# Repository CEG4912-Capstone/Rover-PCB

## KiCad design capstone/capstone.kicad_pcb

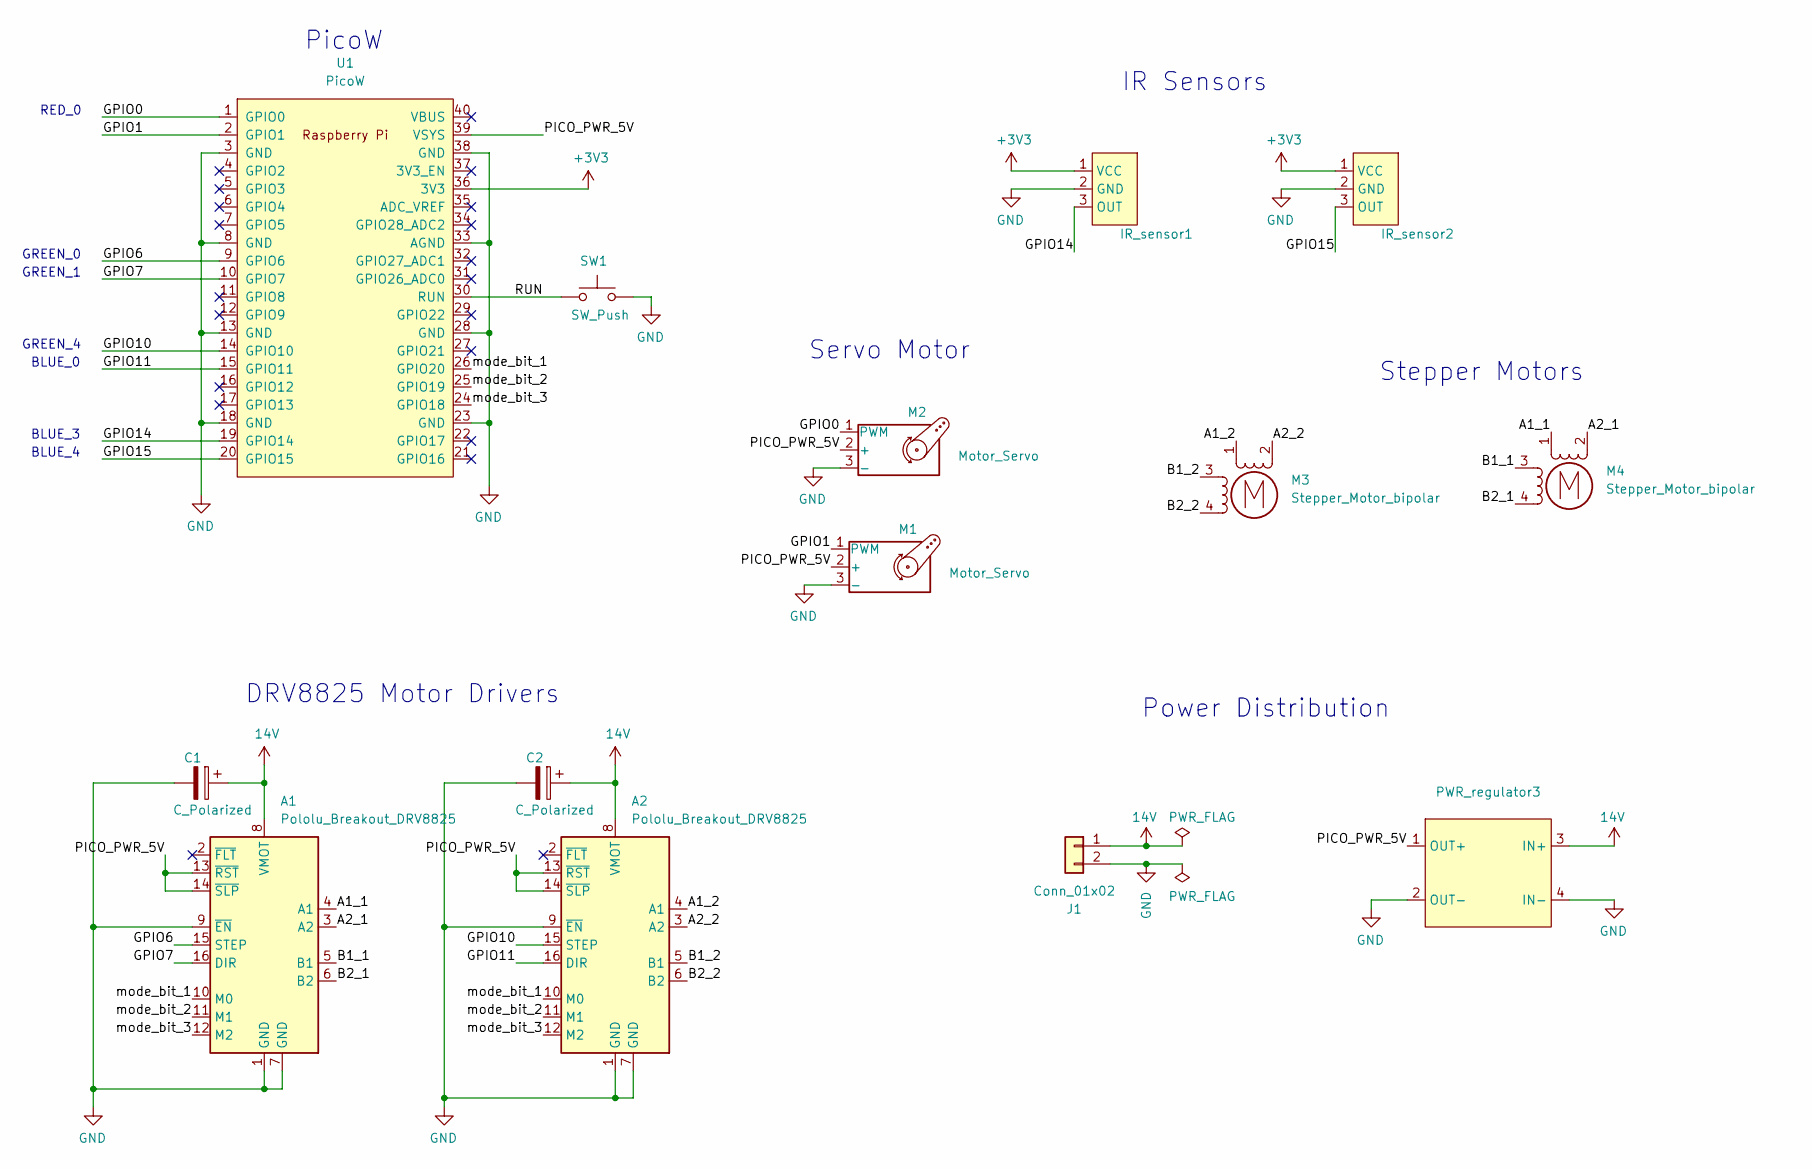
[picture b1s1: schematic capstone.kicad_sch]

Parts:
A1, A2: Pololu_Breakout_DRV8825; Pololu_Breakout-16_15.2x20.3mm
C1, C2: C_Polarized; CP_Radial_D6.3mm_P2.50mm
IR_sensor1, IR_sensor2: PinHeader_1x03_P2.54mm_Vertical
J1: Conn_01x02; AMASS_XT60PW-M_1x02_P7.20mm_Horizontal
M1, M2: Motor_Servo; PinHeader_1x03_P2.54mm_Horizontal
M3, M4: Stepper_Motor_bipolar; PinHeader_1x04_P2.54mm_Horizontal
PWR_regulator3: YAAJ_DCDC_StepDown_LM2596
SW1: SW_Push; SW_Push_1P1T_NO_Vertical_Wuerth_434133025816
U1: PicoW; RPi_PicoW_SMD_TH

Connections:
14V: A1.8 (VMOT), A2.8 (VMOT), C1.1, C2.1, J1.1, PWR_regulator3.3 (IN+)
+3V3: IR_sensor1.1 (VCC), IR_sensor2.1 (VCC), U1.36 (3V3)
/A1_1: A1.4 (A1), M4.1
/A1_2: A2.4 (A1), M3.1
/A2_1: A1.3 (A2), M4.2 (-)
/A2_2: A2.3 (A2), M3.2 (-)
/B1_1: A1.5 (B1), M4.3
/B1_2: A2.5 (B1), M3.3
/B2_1: A1.6 (B2), M4.4
/B2_2: A2.6 (B2), M3.4
/GPIO0: M2.1 (PWM), U1.1 (GPIO0)
/GPIO1: M1.1 (PWM), U1.2 (GPIO1)
/GPIO6: A1.15 (STEP), U1.9 (GPIO6)
/GPIO7: A1.16 (DIR), U1.10 (GPIO7)
/GPIO10: A2.15 (STEP), U1.14 (GPIO10)
/GPIO11: A2.16 (DIR), U1.15 (GPIO11)
/GPIO14: IR_sensor1.3 (OUT), U1.19 (GPIO14)
/GPIO15: IR_sensor2.3 (OUT), U1.20 (GPIO15)
/PICO_PWR_5V: A1.13 (~RST), A1.14 (~SLP), A2.13 (~RST), A2.14 (~SLP), M1.2 (+), M2.2 (+), PWR_regulator3.1 (OUT+), U1.39 (VSYS)
/RUN: SW1.1, U1.30 (RUN)
/mode_bit_1: A1.10 (M0), A2.10 (M0), U1.26 (GPIO20)
/mode_bit_2: A1.11 (M1), A2.11 (M1), U1.25 (GPIO19)
/mode_bit_3: A1.12 (M2), A2.12 (M2), U1.24 (GPIO18)
GND: A1.1 (GND), A1.7 (GND), A1.9 (~EN), A2.1 (GND), A2.7 (GND), A2.9 (~EN), C1.2, C2.2, IR_sensor1.2 (GND), IR_sensor2.2 (GND), J1.2, M1.3 (-), M2.3 (-), PWR_regulator3.2 (OUT-), PWR_regulator3.4 (IN-), SW1.2, U1.3 (GND), U1.8 (GND), U1.13 (GND), U1.18 (GND), U1.23 (GND), U1.28 (GND), U1.33 (AGND), U1.38 (GND)

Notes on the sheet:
BLUE_0
IR Sensors
DRV8825 Motor Drivers
Power Distribution
Servo Motor
GREEN_0
GREEN_4
PicoW
BLUE_4
GREEN_1
Stepper Motors
BLUE_3
RED_0

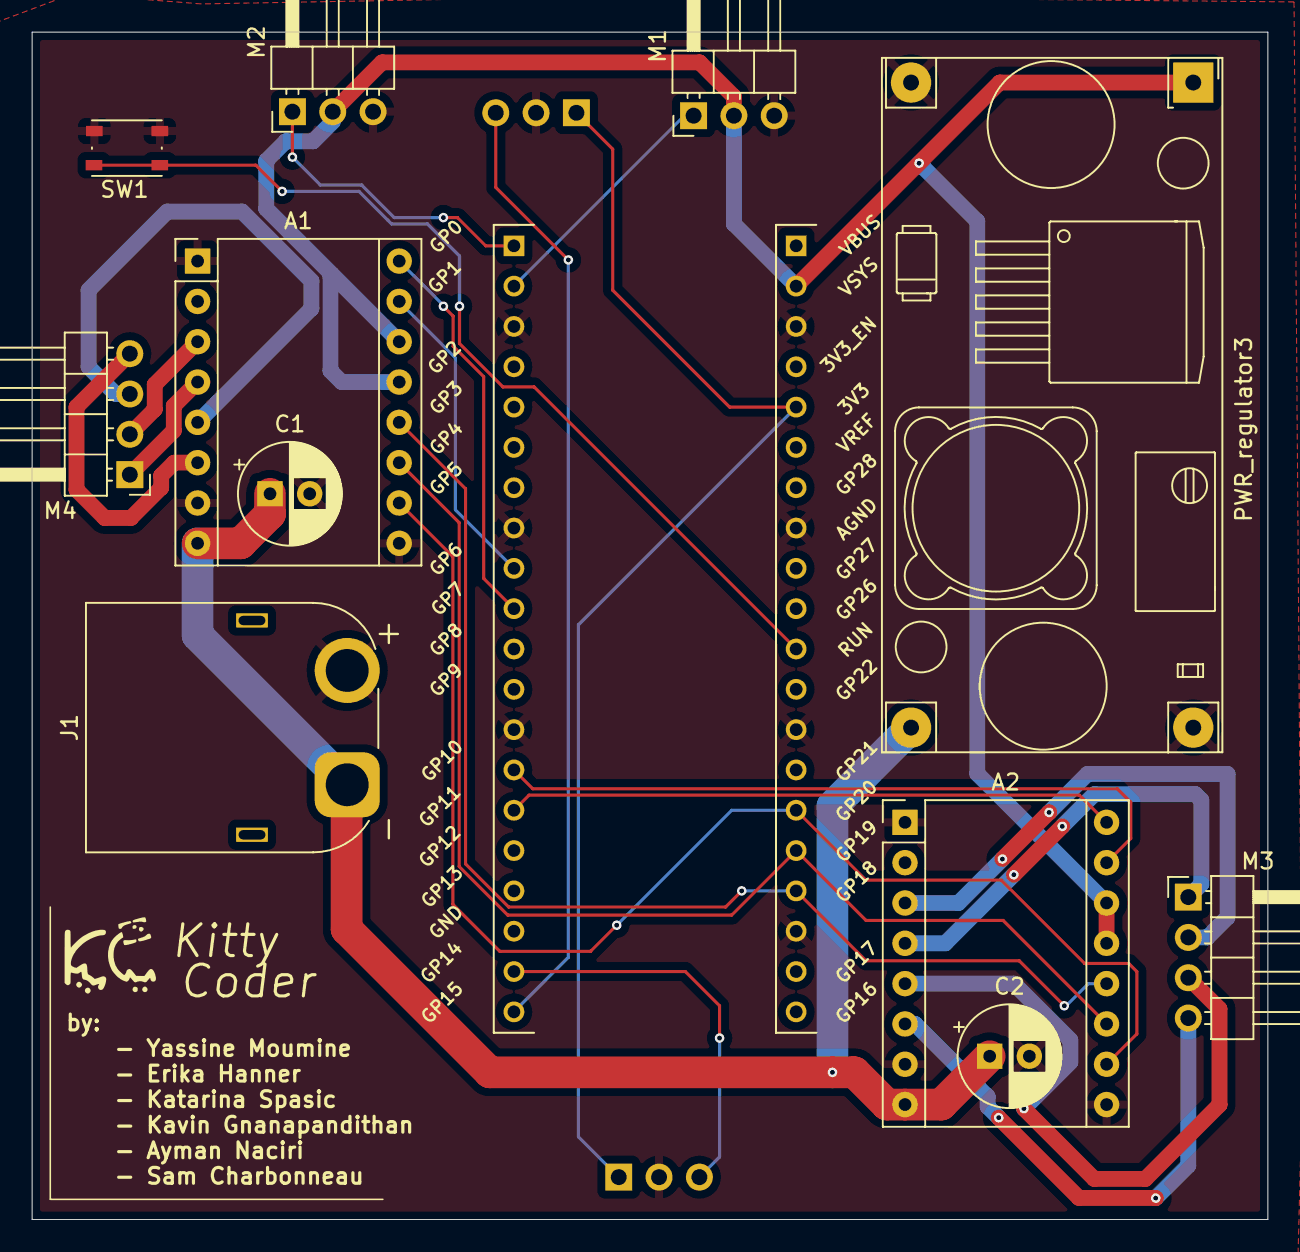
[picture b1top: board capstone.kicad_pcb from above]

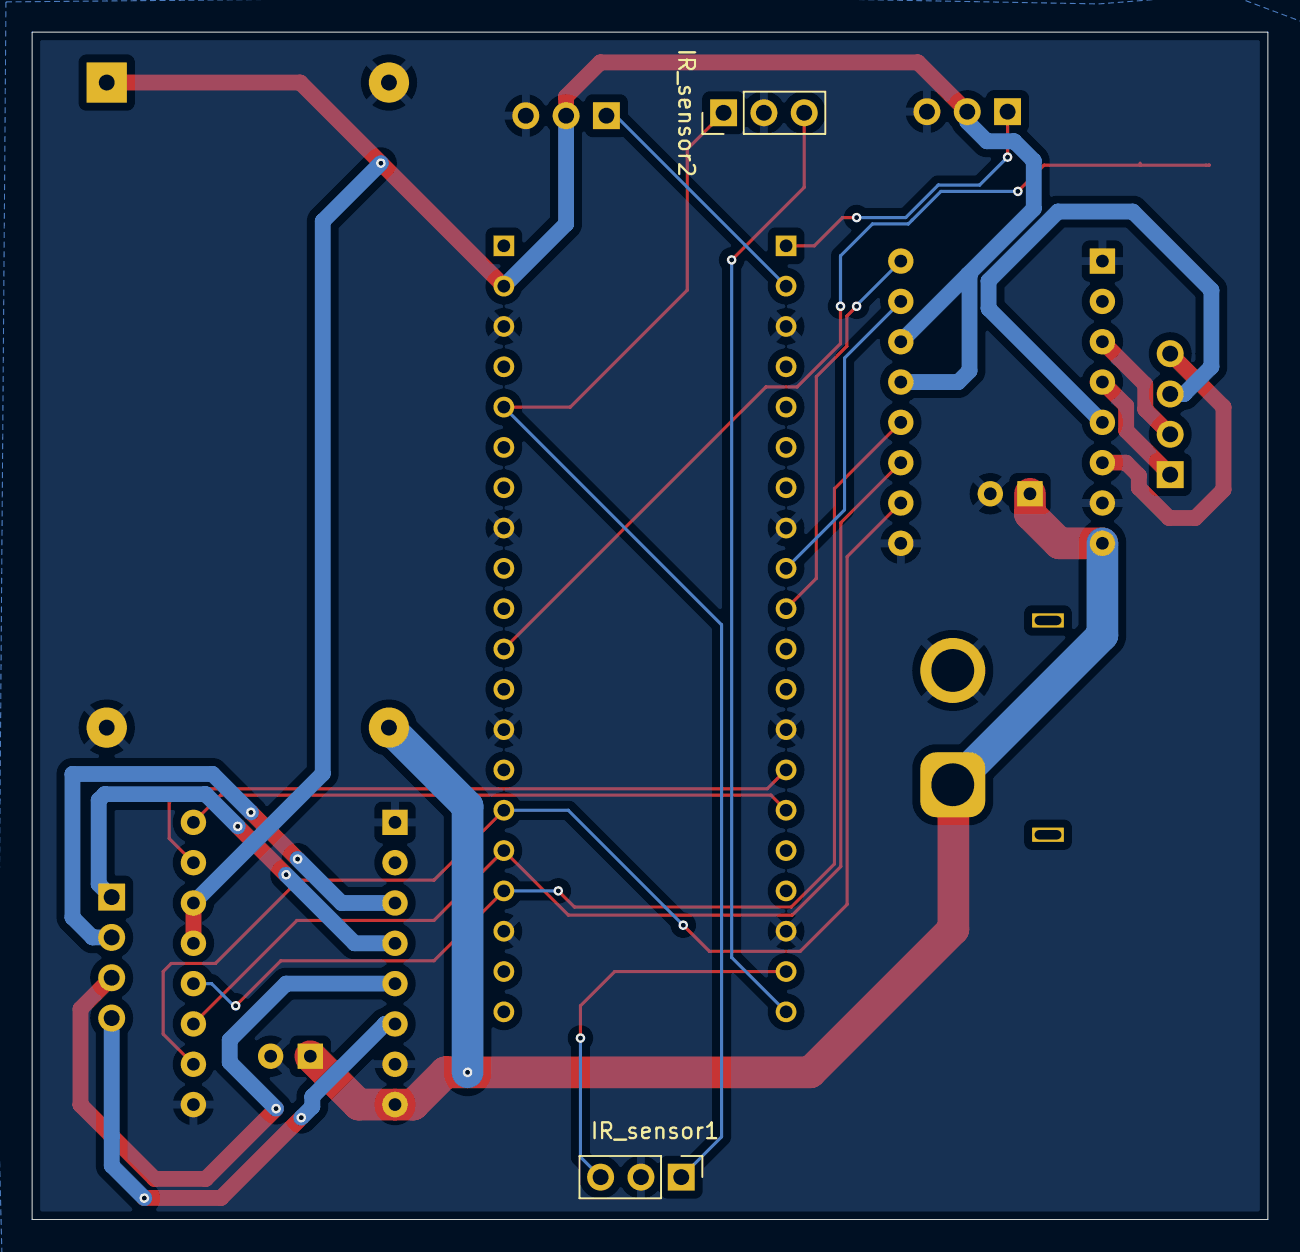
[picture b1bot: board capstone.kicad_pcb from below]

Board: 2 copper layers, 77.9 x 74.8 mm, 14 parts (2 on the bottom side), 24 nets.

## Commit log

2024-11-17 gitignore
2024-11-17 fix gitignore
2024-11-17 kicad project + schematics + footprints + step files
2024-11-21 remove 12v regulators + pcb traces
2024-11-21 final pcb
2024-11-21 text design
